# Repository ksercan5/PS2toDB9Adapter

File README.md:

# PS2toDB9Adapter
Use your Playstation2 Dualshock with Retro Computers (Commodore, Amiga and Atari)

For this project I used Bill Porter's PS2X Arduino Library (http://www.billporter.info/2010/06/05/playstation-2-controller-arduino-library-v1-0/)

For detailed information, please visit (http://seco.gen.tr/2020/07/20/ps2-dualshock-to-c64-joystick-port-mod/)

Use mouse_and_joystick arduino source code to add mouse functionality to your adapter.
To use mouse function (For Amiga only) Press R2 or L2 on Dualshock and move right analog stick. Cross is Left and Square is for Right Mouse Button

For first batch of production (only commodore.gen.tr users), please use v1.1

Other productions use V2 file. (Or you can use the file with mouse support)

# UPDATE:

New double card for C64 will be used to connect two PS2 controllers. Only one Arduino Nano will be enough (Finally tested ok:)

Please download the firmware for double board.

PCBWAY Link: https://www.pcbway.com/project/shareproject/Playstation_PS2_Dualshock_to_DB9__DSUB_9__Adapter_for_Commodore__Amiga_and_Atari_Computers.html

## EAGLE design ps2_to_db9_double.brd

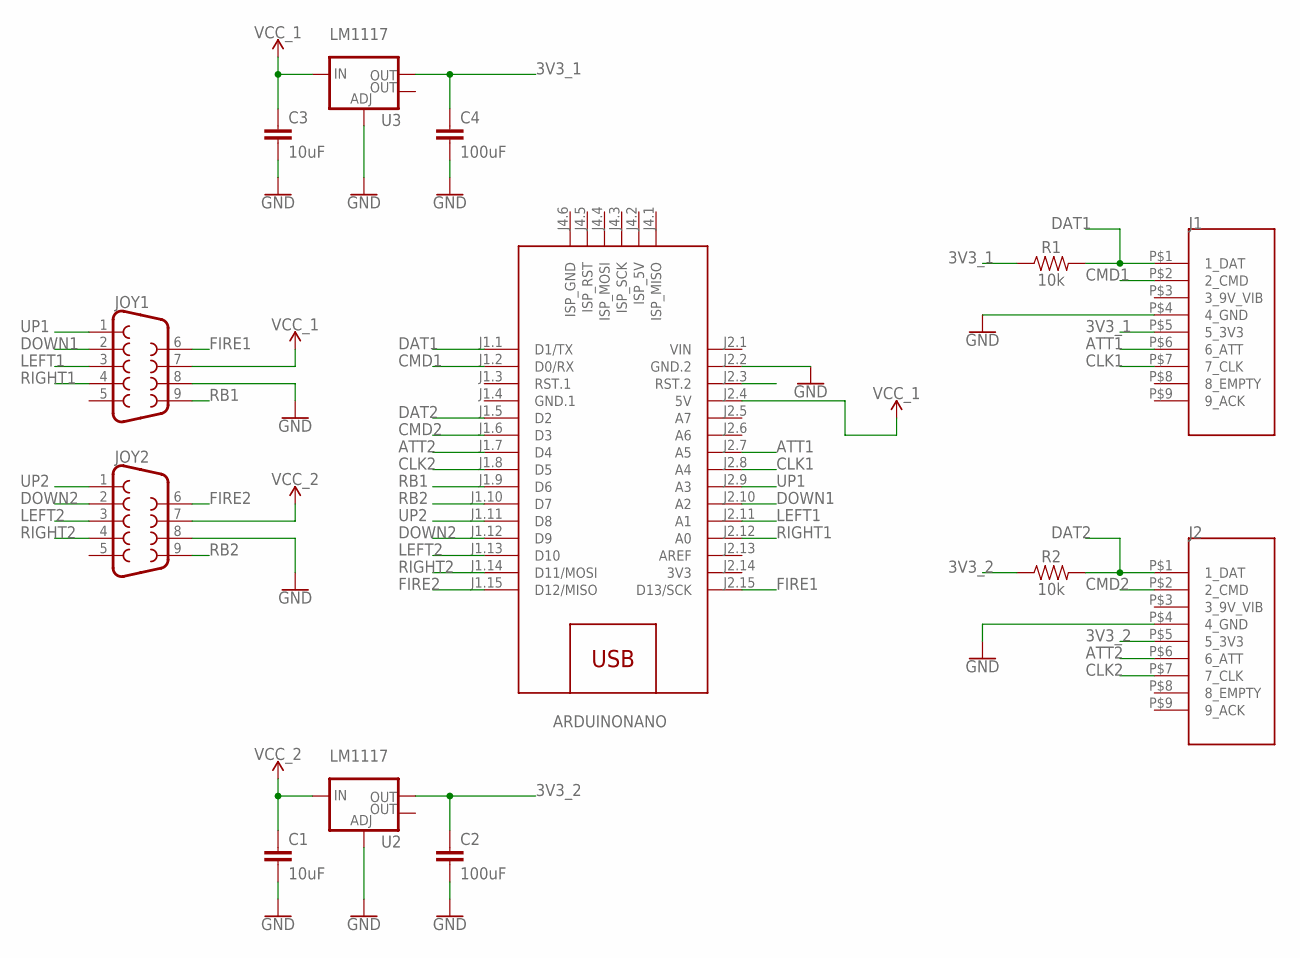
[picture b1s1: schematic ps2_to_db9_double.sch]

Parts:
ARDUINONANO: ARDUINO-NANO-3.0#ISP
C1, C3: 10uF; C025-025X050
C2, C4: 100uF; C025-025X050
J1, J2: PS2_DUALSHOCK_UP
JOY1, JOY2: DB9FEMALE; DB9
R1, R2: 10k; AXIAL-0.3
U2, U3: LM1117; SOT223

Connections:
3V3: ARDUINONANO.J2.14 (3V3)
3V3_1: C4.1, J1.P$5 (5_3V3), R1.P$1 (1), U3.2 (OUT)
3V3_2: C2.1, J2.P$5 (5_3V3), R2.P$1 (1), U2.2 (OUT)
ATT1: ARDUINONANO.J2.7 (A5), J1.P$6 (6_ATT)
ATT2: ARDUINONANO.J1.7 (D4), J2.P$6 (6_ATT)
CLK1: ARDUINONANO.J2.8 (A4), J1.P$7 (7_CLK)
CLK2: ARDUINONANO.J1.8 (D5), J2.P$7 (7_CLK)
CMD1: ARDUINONANO.J1.2 (D0/RX), J1.P$2 (2_CMD)
CMD2: ARDUINONANO.J1.6 (D3), J2.P$2 (2_CMD)
DAT1: ARDUINONANO.J1.1 (D1/TX), J1.P$1 (1_DAT), R1.P$2 (2)
DAT2: ARDUINONANO.J1.5 (D2), J2.P$1 (1_DAT), R2.P$2 (2)
DOWN1: ARDUINONANO.J2.10 (A2), JOY1.2
DOWN2: ARDUINONANO.J1.12 (D9), JOY2.2
FIRE1: ARDUINONANO.J2.15 (D13/SCK), JOY1.6
FIRE2: ARDUINONANO.J1.15 (D12/MISO), JOY2.6
GND: ARDUINONANO.J2.2 (GND.2), C1.2, C2.2, C3.2, C4.2, J1.P$4 (4_GND), J2.P$4 (4_GND), JOY1.8, JOY2.8, U2.1 (ADJ), U3.1 (ADJ)
GND.1: ARDUINONANO.J1.4 (GND.1)
LEFT1: ARDUINONANO.J2.11 (A1), JOY1.3
LEFT2: ARDUINONANO.J1.13 (D10), JOY2.3
RB1: ARDUINONANO.J1.9 (D6), JOY1.9
RB2: ARDUINONANO.J1.10 (D7), JOY2.9
RIGHT1: ARDUINONANO.J2.12 (A0), JOY1.4
RIGHT2: ARDUINONANO.J1.14 (D11/MOSI), JOY2.4
UP1: ARDUINONANO.J2.9 (A3), JOY1.1
UP2: ARDUINONANO.J1.11 (D8), JOY2.1
VCC_1: ARDUINONANO.J2.4 (5V), C3.1, JOY1.7, U3.3 (IN)
VCC_2: C1.1, JOY2.7, U2.3 (IN)
VIN: ARDUINONANO.J2.1 (VIN)

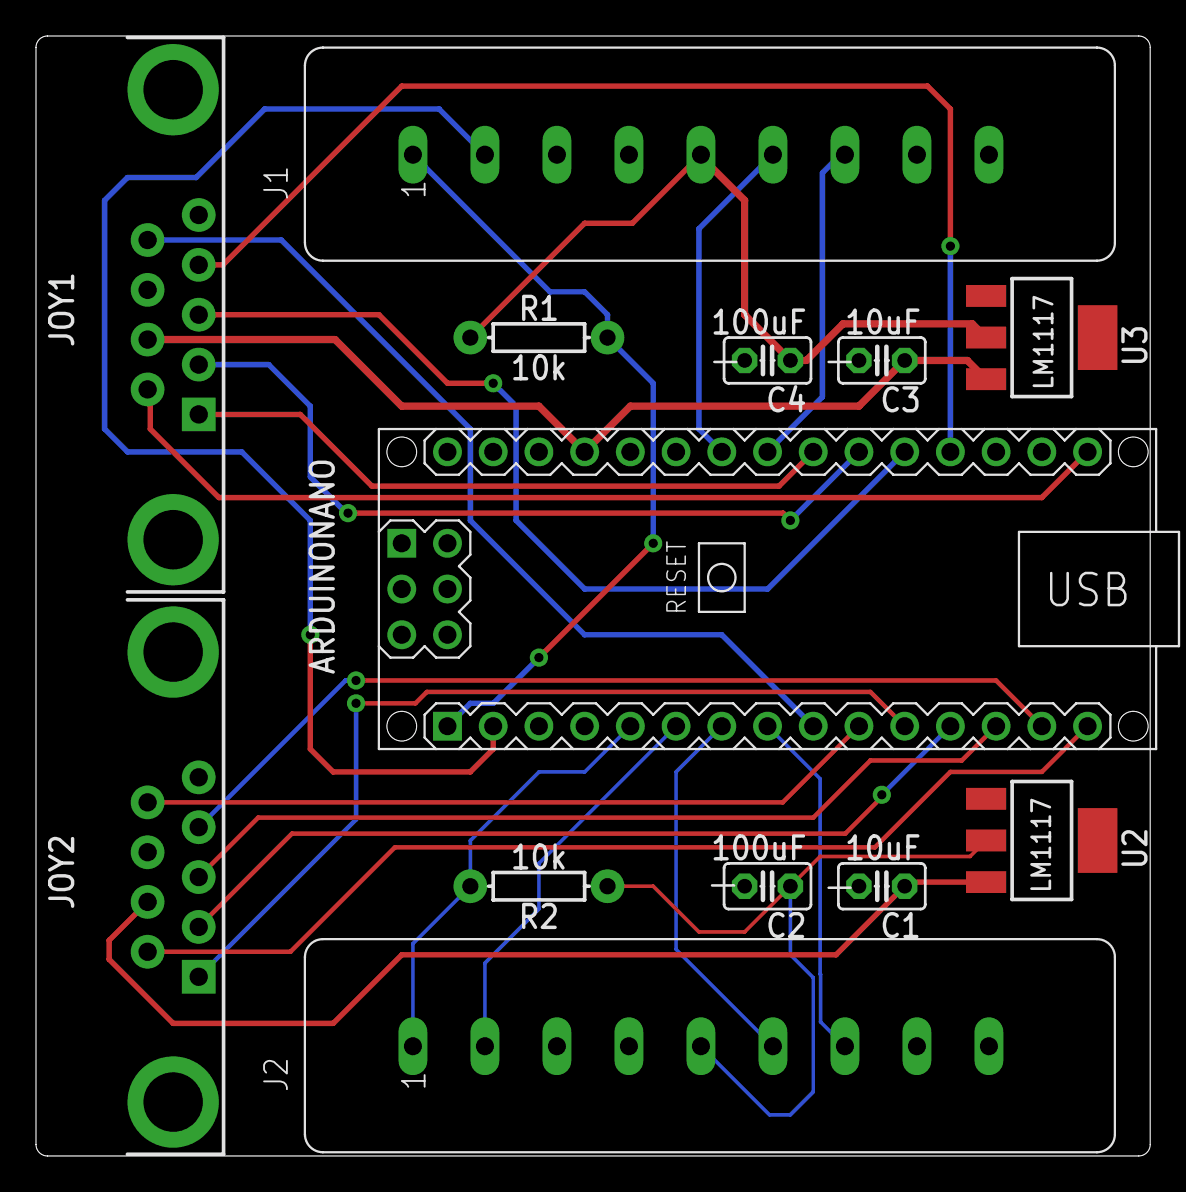
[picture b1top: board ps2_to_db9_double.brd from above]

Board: 2 copper layers, 61.9 x 62.2 mm, 13 parts (0 on the bottom side), 25 nets.

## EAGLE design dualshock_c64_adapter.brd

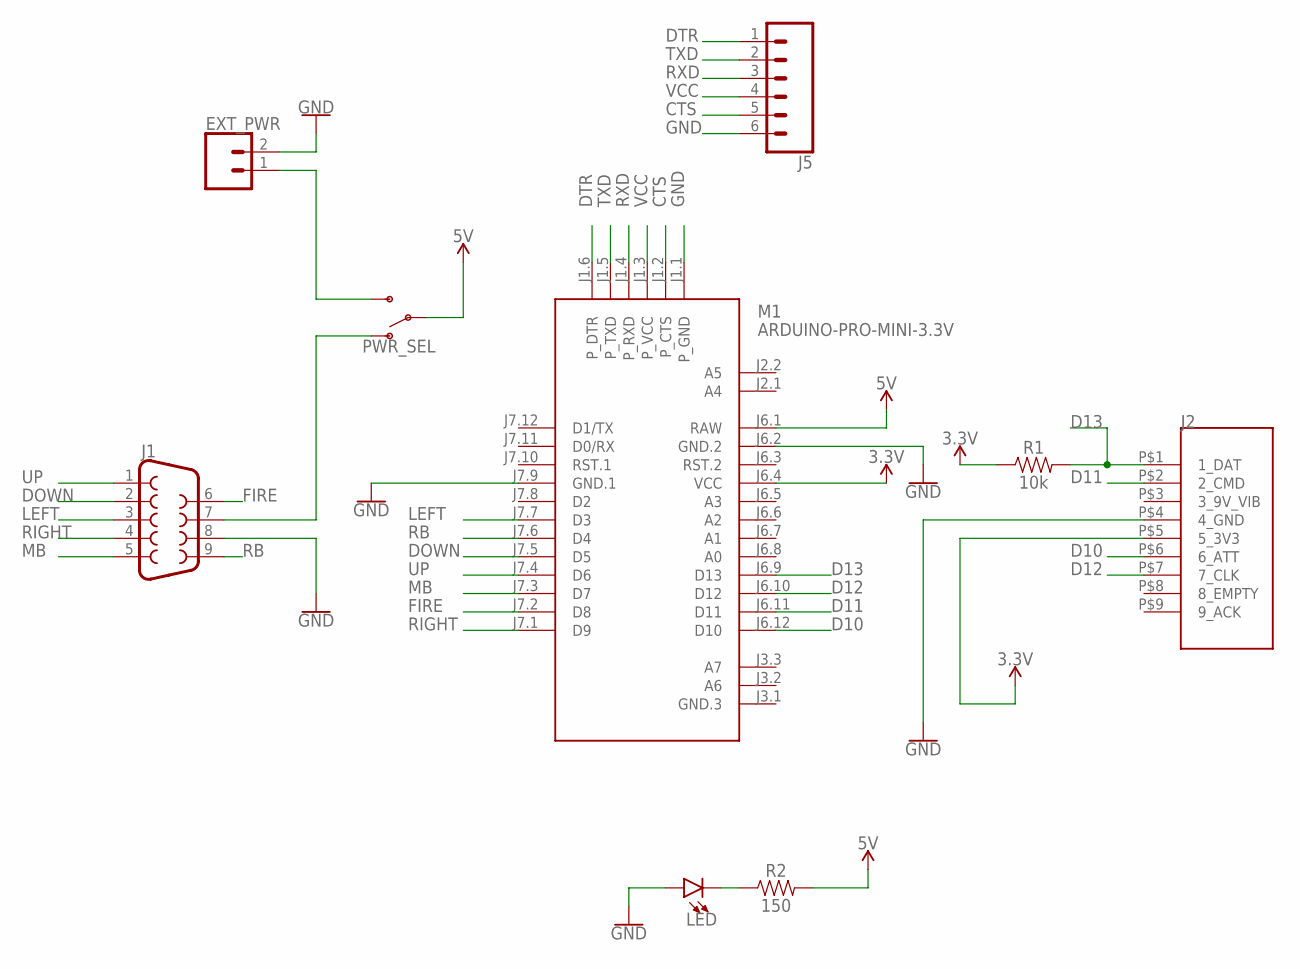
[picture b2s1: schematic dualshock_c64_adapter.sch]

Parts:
EXT_PWR: CONN_02; 1X02
J1: DB9FEMALE; DB9
J2: PS2_DUALSHOCK
J5: CONN_06NO_SILK_FEMALE_PTH; 1X06_NO_SILK
LED: LED5MM; LED_5MM
M1: ARDUINO-PRO-MINI-3.3V; ARDUINO-PRO-MINI
PWR_SEL: SWITCH-SPDT-PTH-11.6X4.0MM; SWITCH_SPDT_PTH_11.6X4.0MM
R1: 10k; AXIAL-0.3
R2: 150; AXIAL-0.3

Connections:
3.3V: J2.P$5 (5_3V3), M1.J6.4 (VCC), R1.P$1 (1)
5V: M1.J6.1 (RAW), PWR_SEL.2, R2.P$2 (2)
CTS: J5.5, M1.J1.2 (P_CTS)
D10: J2.P$6 (6_ATT), M1.J6.12 (D10)
D11: J2.P$2 (2_CMD), M1.J6.11 (D11)
D12: J2.P$7 (7_CLK), M1.J6.10 (D12)
D13: J2.P$1 (1_DAT), M1.J6.9 (D13), R1.P$2 (2)
DOWN: J1.2, M1.J7.5 (D5)
DTR: J5.1, M1.J1.6 (P_DTR)
FIRE: J1.6, M1.J7.2 (D8)
GND: EXT_PWR.2, J1.8, J2.P$4 (4_GND), J5.6, LED.A, M1.J1.1 (P_GND), M1.J6.2 (GND.2), M1.J7.9 (GND.1)
LEFT: J1.3, M1.J7.7 (D3)
MB: J1.5, M1.J7.3 (D7)
unnamed: LED.K (C), R2.P$1 (1)
unnamed: J1.7, PWR_SEL.1 (O)
unnamed: EXT_PWR.1, PWR_SEL.3 (S)
RB: J1.9, M1.J7.6 (D4)
RIGHT: J1.4, M1.J7.1 (D9)
RXD: J5.3, M1.J1.4 (P_RXD)
TXD: J5.2, M1.J1.5 (P_TXD)
UP: J1.1, M1.J7.4 (D6)
VCC: J5.4, M1.J1.3 (P_VCC)

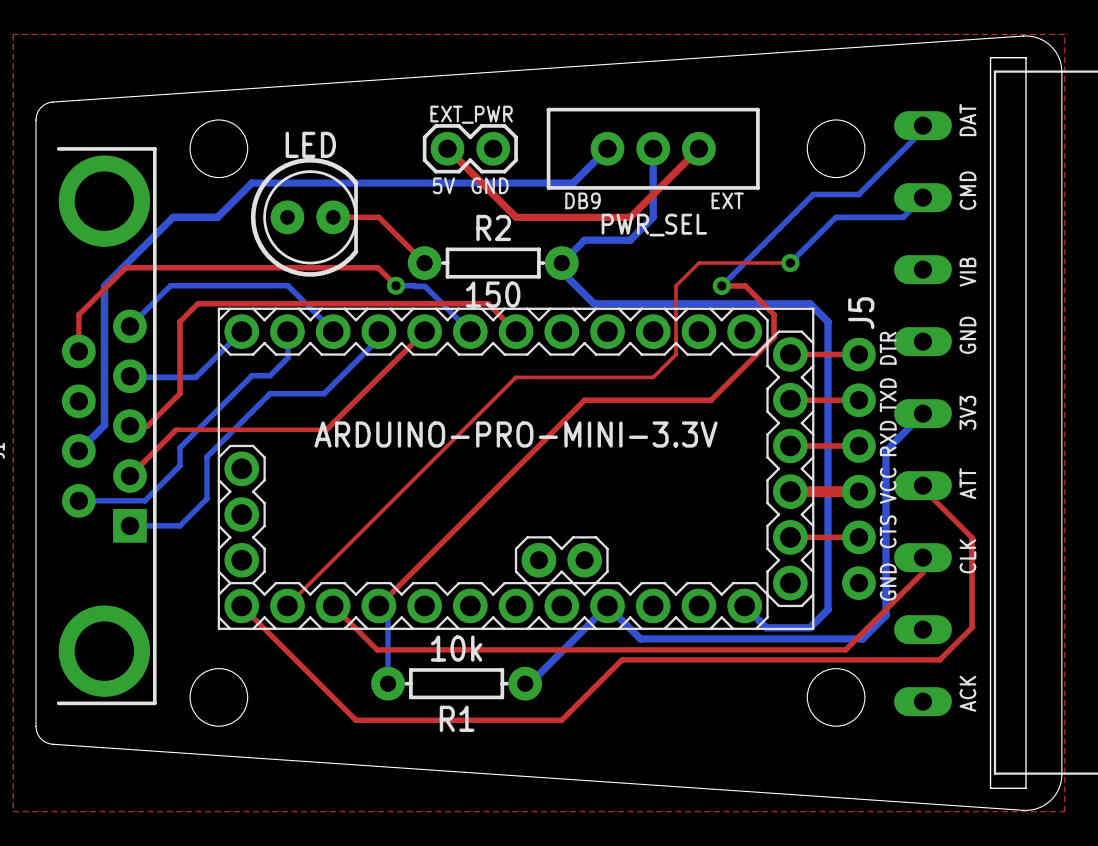
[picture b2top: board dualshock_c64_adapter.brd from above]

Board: 2 copper layers, 57.0 x 43.0 mm, 9 parts (0 on the bottom side), 22 nets.

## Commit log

2020-11-20 Mouse function added
2020-11-20 Some minor changes on PCB design
    Rerouting and dimension change on pins
2020-12-10 Sum bug fixes.
2021-01-26 Update in software, 2nd Fire button for Amiga added
2021-03-01 Updated firmware
2021-03-01 Updated schematics
2021-08-30 3d cover stl files upload

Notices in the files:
parts and their libraries:
SparkFun-Connectors: Licensing: Creative Commons ShareAlike 4.0 International - https://creativecommons.org/licenses/by-sa/4.0
diy-modules: Released under the Creative Commons Attribution 4.0 International License: http://creativecommons.org/licenses/by/4.0
